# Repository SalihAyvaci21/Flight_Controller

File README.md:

#  STM32F405RGT Flight Controller & Development Board

Bu proje, **STM32F405RGT6 (64-pin)** mikrodenetleyicisi tabanlı bir uçuş kartı ve aynı zamanda **entegre ST-LINK** programlayıcısı ile bir geliştirme kartı olarak kullanılabilecek bir donanım platformudur.  

Kart, uçuş modlarını kontrol etmek için kritik sensörler ve genişletilebilir pin yapısıyla tasarlanmıştır. Hem uçuş kontrolü hem de genel gömülü sistem geliştirme için idealdir.

## ✨ Özellikler

- **MCU**: STM32F405RGT6 (Cortex-M4, 1MB Flash, 192KB SRAM, 64-pin LQFP)
- **ST-LINK v2.1**: Dahili programlayıcı (STM32F103CBT tabanlı)
- **Sensörler**:
  - MPU-9250 (9 Eksen IMU - Gyro, Accelerometer, Magnetometer)
  - BMP180 (Barometrik basınç ve sıcaklık sensörü)
  - DHT11 (Nem ve sıcaklık sensörü)
  - (MPU9250 + BMP180 kombinasyonu Türkiye’de kolay bulunabilir)
- **Kablosuz Haberleşme**:
  - **nRF24L01**: Yer istasyonu ile veri alışverişi
  - **GPS**: Neo-8Q (Pin-to-Pin uyumlu M8N alternatifi)
  - Harici anten çıkışı (değiştirilebilir)
- **GPIO**:
  - 4x LED (Uçuş modları için): `PA0`, `PA1`, `PA2`, `PA3`
  - 2x Güç LED’i (3.3V & 5V)
  - Buzzer: `PA8`
  - PWM Çıkışları: `PA0` - `PA3`
  - Boot & Reset düğmeleri
  - Programlama pinleri: `PA13`, `PA14` (SWD)
  - UART4 (ST-LINK üzerinden): `PC10` (TX), `PC11` (RX)
  - Çoğu GPIO **boşta bırakıldı**, kullanıcı entegrasyonu için hazır

---

## 📡 Kablosuz Özellikler

| Bileşen        | Açıklama                                    |
|----------------|---------------------------------------------|
| **nRF24L01**   | Yer istasyonu ile haberleşme için           |
| **Neo-8Q GPS** | Konumlandırma ve uçuş rotası takibi         |
| **Anten Çıkışı**| Harici anten bağlantısı, değiştirilebilir   |

---

## 🛠️ Kullanım Senaryoları

- 🚁 Drone/UAV uçuş kontrolü
- 🧑‍💻 STM32 geliştirme platformu
- 📡 Kablosuz veri iletimi prototipleri
- 📦 Sensör entegrasyonu için araştırma & eğitim projeleri

---

## 🔌 Pinout & Peripherals

| Fonksiyon             | Pinler             |
|-----------------------|---------------------|
| Uçuş Modu LED’leri    | PA0, PA1, PA2, PA3  |
| Güç LED’leri          | 3.3V, 5V            |
| Buzzer                | PA8                 |
| Boot & Reset Butonları| GPIO kontrollü      |
| PWM Çıkışları         | PA0 - PA3           |
| SWD Programlama       | PA13, PA14          |
| UART4 (ST-LINK)       | PC10 (TX), PC11 (RX)|
| GPS                   | Harici bağlantı     |
| nRF24L01              | SPI bağlantısı      |

---

## ⚙️ Programlama & Debug

- **ST-LINK Dahili**
  - STM32F103CBT tabanlı entegre ST-LINK
  - SWD pinleri dışarı alınmıştır (`PA13`, `PA14`)
  - STM32CubeProgrammer veya OpenOCD ile uyumlu
- **UART Debugging**
  - UART4 üzerinden ST-LINK’e bağlantı

---

## 📦 Entegrasyon & Genişletilebilirlik

- Tüm kritik uçuş sensörleri **entegre edilmiştir**  
- Çoğu GPIO boşta bırakılmıştır – ek donanımlar ve özel modüller için kullanılabilir
- Geliştiriciler kendi devrelerini veya sensörlerini kolayca entegre edebilir

---

## 🚀 Başlarken

1. USB üzerinden bilgisayara bağlanın (ST-LINK otomatik tanınır)
2. STM32CubeProgrammer ile firmware yükleyin
3. Harici sensörleri ve modülleri GPIO’lara bağlayın
4. UART4 ile seri haberleşmeyi başlatın

---

## 📃 Lisans

Bu proje tamamen açık kaynaklıdır. İsteyen herkes geliştirme ve entegrasyon yapabilir.

---

## 📝 Notlar
- MPU9250 ve BMP180 Türkiye’de kolay bulunabilir ve birlikte modül olarak satılmaktadır.
- GPS için Neo-8Q kullanılmıştır; Pin-to-Pin uyumlu M8N de kullanılabilir.

---

STM32F405RGT Flight Controller & Development Board
This project is a hardware platform based on the STM32F405RGT6 (64-pin) microcontroller, designed as both a flight controller and a development board with an integrated ST-LINK programmer.

The board is equipped with critical sensors for flight modes and an extendable pin structure, making it ideal for both flight control and general embedded system development.

✨ Features
MCU: STM32F405RGT6 (Cortex-M4, 1MB Flash, 192KB SRAM, 64-pin LQFP)

ST-LINK v2.1: Built-in programmer (based on STM32F103CBT)

Sensors:

MPU-9250 (9-axis IMU - Gyroscope, Accelerometer, Magnetometer)

BMP180 (Barometric pressure and temperature sensor)

DHT11 (Humidity and temperature sensor)

(MPU9250 + BMP180 combo is widely available)

Wireless Communication:

nRF24L01: For data exchange with ground station

GPS: Neo-8Q (Pin-compatible with M8N alternative)

External antenna connector (replaceable)

GPIO:

4x LEDs (for flight modes): PA0, PA1, PA2, PA3

2x Power LEDs (3.3V & 5V)

Buzzer: PA8

PWM Outputs: PA0 - PA3

Boot & Reset buttons

Programming pins: PA13, PA14 (SWD)

UART4 (via ST-LINK): PC10 (TX), PC11 (RX)

Most GPIOs are left free for user integration

📡 Wireless Features
Component	Description
nRF24L01	Communication with ground station
Neo-8Q GPS	Positioning and flight route tracking
Antenna Out	External antenna connector, replaceable

🛠️ Use Cases
🚁 Drone/UAV flight control

🧑‍💻 STM32 development platform

📡 Wireless data transmission prototypes

📦 Research & educational projects for sensor integration

🔌 Pinout & Peripherals
Function	Pins
Flight Mode LEDs	PA0, PA1, PA2, PA3
Power LEDs	3.3V, 5V
Buzzer	PA8
Boot & Reset Buttons	GPIO controlled
PWM Outputs	PA0 - PA3
SWD Programming	PA13, PA14
UART4 (ST-LINK)	PC10 (TX), PC11 (RX)
GPS	External connection
nRF24L01	SPI interface

⚙️ Programming & Debug
Built-in ST-LINK

Based on STM32F103CBT

SWD pins exposed (PA13, PA14)

Compatible with STM32CubeProgrammer and OpenOCD

UART Debugging

Connected via UART4 to ST-LINK

📦 Integration & Expandability
All critical flight sensors are integrated

Most GPIOs are left free – ready for additional hardware or custom modules

Developers can easily integrate their own circuits or sensors

🚀 Getting Started
Connect to PC via USB (ST-LINK auto-detected)

Flash firmware using STM32CubeProgrammer

Connect external sensors and modules to GPIOs

Start serial communication via UART4

📃 License
This project is fully open-source. Anyone is free to develop and integrate.

📝 Notes
MPU9250 and BMP180 are widely available and often sold as combined modules.

Neo-8Q GPS is used; Pin-compatible M8N can also be used.

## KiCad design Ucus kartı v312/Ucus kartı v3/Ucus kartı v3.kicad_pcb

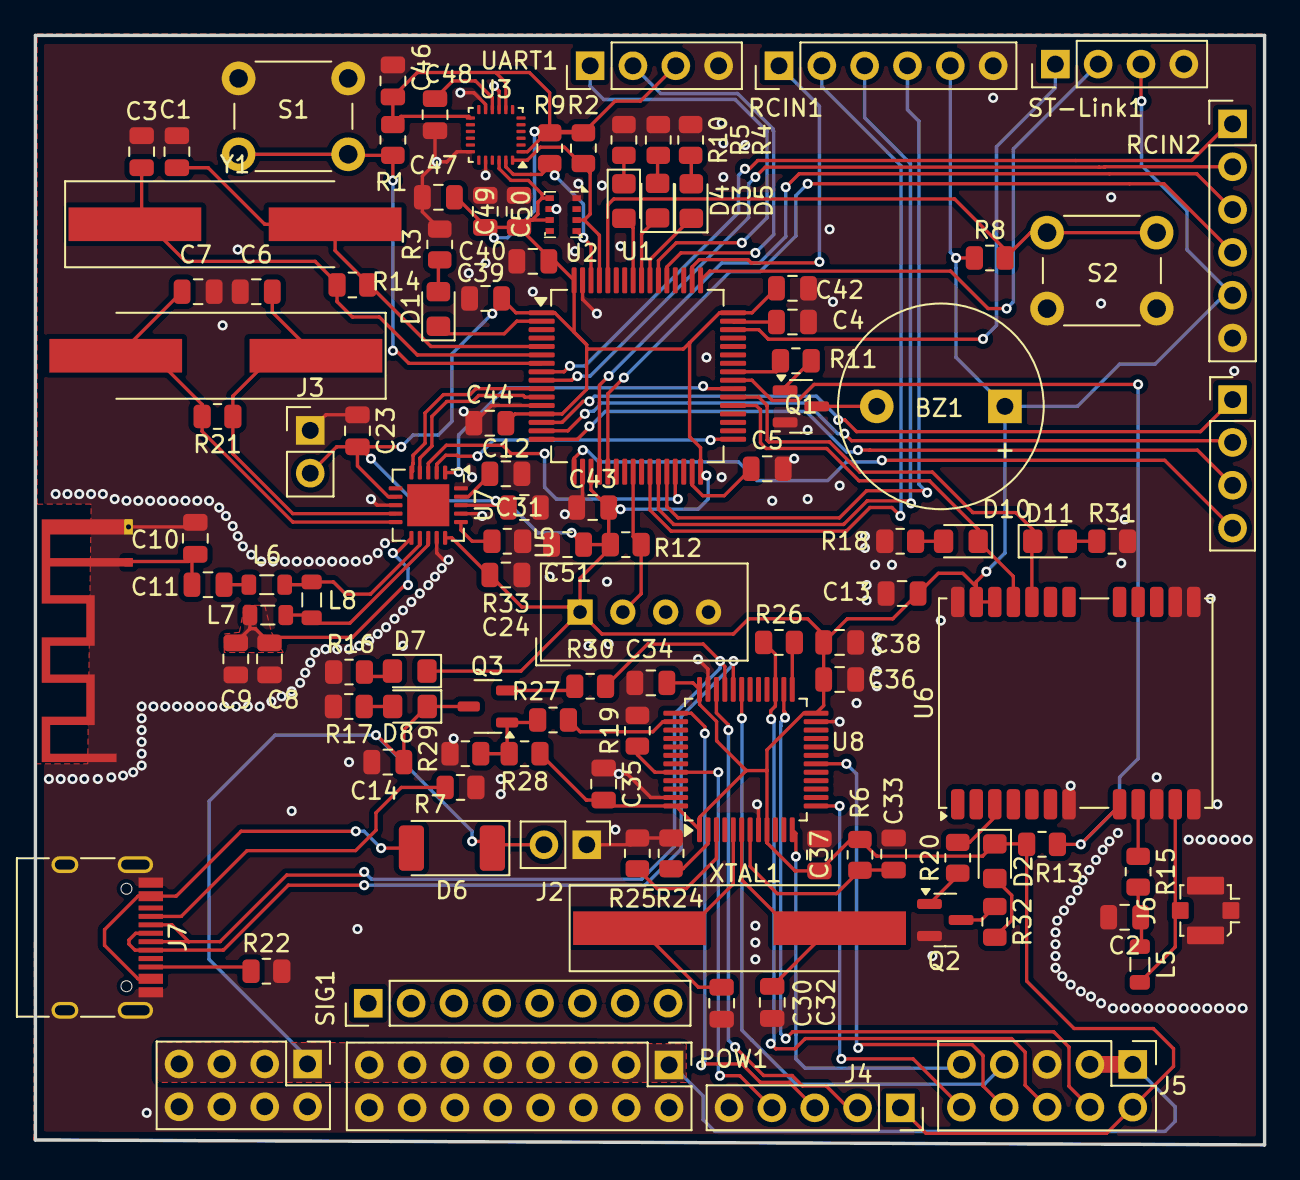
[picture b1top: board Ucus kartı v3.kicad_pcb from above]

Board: 2 copper layers, 72.9 x 65.8 mm, 113 parts (0 on the bottom side), 91 nets.

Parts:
ANT1: SWRA117D; Texas_SWRA117D_2.4GHz_Left
BZ1: Buzzer; Buzzer_12x9.5RM7.6
C1, C3, C6, C7: 20pF; C_0805_2012Metric
C2: 10uF; C_0805_2012Metric
C4, C5: 2.2uF; C_0805_2012Metric
C8: 2.2nF; C_0805_2012Metric
C9: 4.7pF; C_0805_2012Metric
C10: 1pF; C_0805_2012Metric
C11: 1.5pF; C_0805_2012Metric
C12: 33nF; C_0805_2012Metric
C13: 1uF; C_0805_2012Metric
C14, C46: 10nF; C_0805_2012Metric
C23, C24, C31, C33, C34, C35, C36, C37, C38, C39, C40, C42, C43, C44, C47, C48, C49, C50, C51: 100nF; C_0805_2012Metric
C30, C32: 18pF; C_0805_2012Metric
D1, D7, D8: LH_R974-LP-1; LED_0805_2012Metric_Pad1.15x1.40mm_HandSolder
D2: G/LTST-C171KGKT; LED_0805_2012Metric_Pad1.15x1.40mm_HandSolder
D3, D5: B/LTST-C170TBKT; LED_0805_2012Metric_Pad1.15x1.40mm_HandSolder
D4, D10, D11: R/LH_R974-LP-1; LED_0805_2012Metric_Pad1.15x1.40mm_HandSolder
D6: D_Schottky; D_MELF
J2, J3: Conn_01x02; PinHeader_1x02_P2.54mm_Vertical
J4: Conn_01x05; PinSocket_1x05_P2.54mm_Vertical
J5: Conn_02x05_Odd_Even; PinHeader_2x05_P2.54mm_Vertical
J6: U_FL-R-SMT_10_; U.FL_Molex_MCRF_73412-0110_Vertical
J7: USB_C_Receptacle_USB2.0_14P; USB_C_Receptacle_HRO_TYPE-C-31-M-12
L5: 27nH; L_0805_2012Metric
L6: 3.9nH; L_0805_2012Metric
L7: 2.7nH; L_0805_2012Metric
L8: 8.2nH; L_0805_2012Metric
POW1: Conn_02x08_Odd_Even; PinHeader_2x08_P2.54mm_Vertical
PWM_POW1: Conn_02x04_Odd_Even; PinHeader_2x04_P2.54mm_Vertical
PWM_SIG1: Conn_01x04; PinHeader_1x04_P2.54mm_Vertical
Q1, Q2: Q_NPN_BEC; SOT-23
Q3: BC817-25-TP; SOT-23-3
R1, R8, R13: 10k; R_0805_2012Metric
R2, R9, R11, R12, R20: 4.7k; R_0805_2012Metric
R3, R4, R5, R10, R16, R18, R21, R31, R32: 470R; R_0805_2012Metric
R6, R19: 100K; R_0805_2012Metric
R7, R22: 5.1k; R_0805_2012Metric
R14: 1M; R_0805_2012Metric
R15: 10R; R_0805_2012Metric
R17: 1k; R_0805_2012Metric
R24, R25, R28: 10K; R_0805_2012Metric
R26, R27: 100R; R_0805_2012Metric
R29: 39K; R_0805_2012Metric
R30: 15K; R_0805_2012Metric
R33: 22k; R_0805_2012Metric
RCIN1, RCIN2: Conn_01x06; PinHeader_1x06_P2.54mm_Vertical
S1, S2: KS-01Q-01_Obsolete; SW_PUSH_6mm_H4.3mm
SIG1: Conn_01x08; PinHeader_1x08_P2.54mm_Vertical
ST-Link1: Conn_01x04; PinHeader_1x04_P2.54mm_Vertical
U1: STM32F405RGTx; LQFP-64_10x10mm_P0.5mm
U2: BMP280; Bosch_LGA-8_2x2.5mm_P0.65mm_ClockwisePinNumbering
U3: MPU-9250; InvenSense_QFN-24_3x3mm_P0.4mm
U5: DHT11; Aosong_DHT11_5.5x12.0_P2.54mm
U6: NEO-8Q; ublox_NEO
U7: NRF24L01; QFN-20-1EP_4x4mm_P0.5mm_EP2.5x2.5mm
U8: STM32F103CBTx; LQFP-48_7x7mm_P0.5mm
UART1: Conn_01x04; PinHeader_1x04_P2.54mm_Vertical
XTAL1: NX3225GD-8MHZ-STD-CRA-3; Crystal_SMD_HC49-SD_HandSoldering
Y1, Y2: 16MHz; Crystal_SMD_HC49-SD_HandSoldering

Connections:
+3.3V: BZ1.1 (-), C13.2, C23.2, C24.2, C31.2, C34.2, C35.2, C36.2, C37.2, C38.2, C39.2, C40.2, C42.2, C43.2, C44.2, C46.2, C47.2, C49.2, C50.2, C51.1, D2.1, D7.1, J3.2, J4.1, J5.2, R1.1, R2.1, R6.1, R8.1, R9.1, R12.2, R13.2, R28.1, RCIN1.5, RCIN2.5, ST-Link1.3, U1.1 (VBAT), U1.13 (VDDA), U1.19 (VDD), U1.32 (VDD), U1.48 (VDD), U1.64 (VDD), U2.6 (VDDIO), U2.8 (VDD), U3.1 (RESV_VDDIO), U3.8 (VDDIO), U3.13 (VDD), U3.22 (~CS), U5.1 (VDD), U6.22 (V_BCKP), U6.23 (VCC), U7.7 (VDD), U7.15 (VDD), U7.18 (VDD), U8.1 (VBAT), U8.9 (VDDA), U8.24 (VDD), U8.36 (VDD), U8.48 (VDD), UART1.3
+5V: C14.1, D6.1 (K), D8.1, J2.2, J5.1, J5.3, POW1.1, POW1.3, POW1.5, POW1.7, POW1.9, POW1.11, POW1.13, POW1.15, PWM_POW1.1, PWM_POW1.3, PWM_POW1.5, PWM_POW1.7, Q3.3 (C)
/KABLOSUZ HABERLEŞME/RF_IN: J6.1, L5.2, U6.11 (RF_IN)
/KABLOSUZ HABERLEŞME/VCC_RF: R15.1, U6.9 (VCC_RF)
/stlink/BOOT0: J4.4, R19.1, U8.44 (BOOT0)
/stlink/RENUM: R27.2, U8.38 (PA15)
/stlink/SWCLK: J4.3, U8.37 (PA14)
/stlink/SWDIO: J4.2, U8.34 (PA13)
/stlink/T_DIO: J5.6, R26.1, U8.27 (PB14)
/stlink/T_RESET: J5.8, U8.18 (PB0)
/stlink/T_RX: J5.10, U8.13 (PA3)
/stlink/T_SWCLK: J5.4, U8.26 (PB13)
/stlink/T_SWO: J5.7, U8.31 (PA10)
/stlink/T_TX: J5.9, U8.12 (PA2)
/stlink/X0: C32.2, U8.6 (PD1), XTAL1.2
/stlink/XI: C30.2, U8.5 (PD0), XTAL1.1
ADC1_IN10: RCIN2.1, U1.8 (PC0)
ADC1_IN11: RCIN2.2, U1.9 (PC1)
ADC1_IN12: RCIN2.4, U1.21 (PA5)
ADC1_IN13: RCIN2.3, U1.20 (PA4)
BOOT0: R8.2, S2.2, U1.60 (BOOT0)
Buzzer: R11.1, U1.41 (PA8)
D+: J7.A7 (D-), J7.B7 (D-), R30.2, U8.33 (PA12)
D-: J7.A6 (D+), J7.B6 (D+), U8.32 (PA11)
DHT_DATA: R12.1, U1.24 (PC4), U5.2 (DATA)
GND: ANT1.2 (GND), C1.2, C2.2, C3.2, C4.2, C5.2, C6.2, C7.2, C8.1, C9.1, C10.1, C12.2, C13.1, C14.2, C23.1, C24.1, C30.1, C31.1, C32.1, C33.1, C34.1, C35.1, C36.1, C37.1, C38.1, C39.1, C40.1, C42.1, C43.1, C44.1, C46.1, C47.1, C48.1, C49.1, C50.1, C51.2, J2.1, J3.1, J4.5, J5.5, J6.2, J7.A1 (GND), J7.A12 (GND), J7.B1 (GND), J7.B12 (GND), J7.S1 (SHIELD), POW1.2, POW1.4, POW1.6, POW1.8, POW1.10, POW1.12, POW1.14, POW1.16, PWM_POW1.2, PWM_POW1.4, PWM_POW1.6, PWM_POW1.8, Q1.2 (E), Q2.2 (E), R3.2, R4.2, R5.2, R7.2, R10.2, R16.2, R17.2, R18.1, R19.2, R22.2, R24.1, R25.1, R29.2, R31.2, R33.2, RCIN1.6, RCIN2.6, S1.1, S2.1, ST-Link1.4, U1.12 (VSSA), U1.18 (VSS), U1.63 (VSS), U2.1 (GND), U2.7 (GND), U3.9 (AD0/MISO), U3.11 (FSYNC), U3.18 (GND), U3.20 (RESV_GND), U5.4 (GND), U6.7 (VDD_USB), U6.10 (GND), U6.12 (GND), U6.13 (GND), U6.14 (LNA_EN), U6.24 (GND), U7.8 (VSS), U7.14 (VSS), U7.17 (VSS), U7.20 (VSS), U8.8 (VSSA), U8.23 (VSS), U8.35 (VSS), U8.47 (VSS), UART1.4
GPS_RESET: R13.1, U1.40 (PC9), U6.8 (~RESET)
I2C1_SCL: R9.2, U1.62 (PB9), U2.4 (SCK), U3.23 (SCL/SCLK)
I2C1_SDA: R2.2, U1.61 (PB8), U2.3 (SDI), U3.24 (SDA/MOSI)
LED_1: D5.1, U1.55 (PB3)
LED_2: D3.1, U1.56 (PB4)
LED_3: D4.2 (A), U1.57 (PB5)
LED_PC13: D1.1, U1.2 (PC13)
unnamed: ANT1.1 (SIG), C10.2, C11.1
unnamed: BZ1.2 (+), Q1.3 (C)
unnamed: C2.1, L5.1, R15.2
unnamed: C11.2, L6.2
unnamed: D1.2, R3.1
unnamed: D2.2, R32.2
unnamed: D3.2, R5.1
unnamed: D4.1 (K), R10.1
unnamed: D5.2, R4.1
unnamed: D7.2, R16.1
unnamed: D8.2, R17.1
unnamed: D10.2, R18.2
unnamed: D11.2, R31.1
unnamed: J7.A5 (CC1), R7.1
unnamed: J7.B5 (CC2), R22.1
unnamed: Q1.1 (B), R11.2
unnamed: Q2.1 (B), R20.1
unnamed: Q2.3 (C), R32.1
unnamed: Q3.1 (B), R27.1, R28.2, R29.1
unnamed: Q3.2 (E), R30.1
unnamed: C5.1, U1.31 (VCAP_1)
unnamed: C4.1, U1.47 (VCAP_2)
unnamed: C48.2, U3.10 (REGOUT)
unnamed: R20.2, U6.3 (TIMEPULSE)
unnamed: L6.1, L8.1, U7.12 (ANT1)
unnamed: L7.1, L8.2, U7.13 (ANT2)
unnamed: C12.1, U7.19 (DVDD)
unnamed: R33.1, U7.16 (IREF)
unnamed: C7.1, R21.2, U7.10 (XC1), Y2.2
unnamed: C6.1, R21.1, U7.9 (XC2), Y2.1
unnamed: C33.2, R6.2, U8.7 (NRST)
unnamed: R26.2, U8.25 (PB12)
unnamed: R24.2, U8.2 (PC13)
unnamed: R25.2, U8.3 (PC14)
OSC_IN_16: C1.1, R14.1, U1.5 (PH0), Y1.2
OSC_OUT_16: C3.1, R14.2, U1.6 (PH1), Y1.1
RESET: R1.2, S1.2, U1.7 (NRST)
SPI2_CE: U1.39 (PC8), U7.1 (CE)
SPI2_CSN: U1.33 (PB12), U7.2 (CSN)
SPI2_MISO: U1.10 (PC2), U7.5 (MISO)
SPI2_MOSI: U1.11 (PC3), U7.4 (MOSI)
SPI2_SCK: U1.29 (PB10), U7.3 (SCK)
SWCLK: ST-Link1.2, U1.49 (PA14)
SWDIO: ST-Link1.1, U1.46 (PA13)
TIM2_CH1: RCIN1.1, U1.50 (PA15)
TIM2_CH2: RCIN1.2, U1.26 (PB0)
TIM3_CH1: RCIN1.3, U1.27 (PB1)
TIM3_CH2: RCIN1.4, U1.28 (PB2)
TIM5_CH1: PWM_SIG1.4, U1.17 (PA3)
TIM5_CH2: PWM_SIG1.3, U1.16 (PA2)
TIM5_CH3: PWM_SIG1.2, U1.15 (PA1)
TIM5_CH4: PWM_SIG1.1, U1.14 (PA0)
UART1_RX: U1.54 (PD2), UART1.1
UART1_TX: U1.53 (PC12), UART1.2
UART6_RX: D11.1, U1.38 (PC7), U6.20 (TXD/SPI_MISO)
UART6_TX: D10.1, U1.37 (PC6), U6.21 (RXD/SPI_MOSI)
VBUS: D6.2 (A), J7.A4 (VBUS), J7.A9 (VBUS), J7.B4 (VBUS), J7.B9 (VBUS)
VDD_PA: C8.2, C9.2, L7.2, U7.11 (VDD_PA)

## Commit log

2025-07-18 README.md
